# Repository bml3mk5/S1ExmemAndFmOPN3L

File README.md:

# Extended RAM & FM Synthesis Card for HITACHI MB-S1 (OPN3-L (YMF288) Version)

This is the extension card for HITACHI MB-S1 and Limelight. This is assembled two circuits
which are extended RAMs and FM Synthesis (YAMAHA YMF288(OPN3-L)). You can use two circuits, or just one of them.

## Used Tools

* KiCAD Version 5

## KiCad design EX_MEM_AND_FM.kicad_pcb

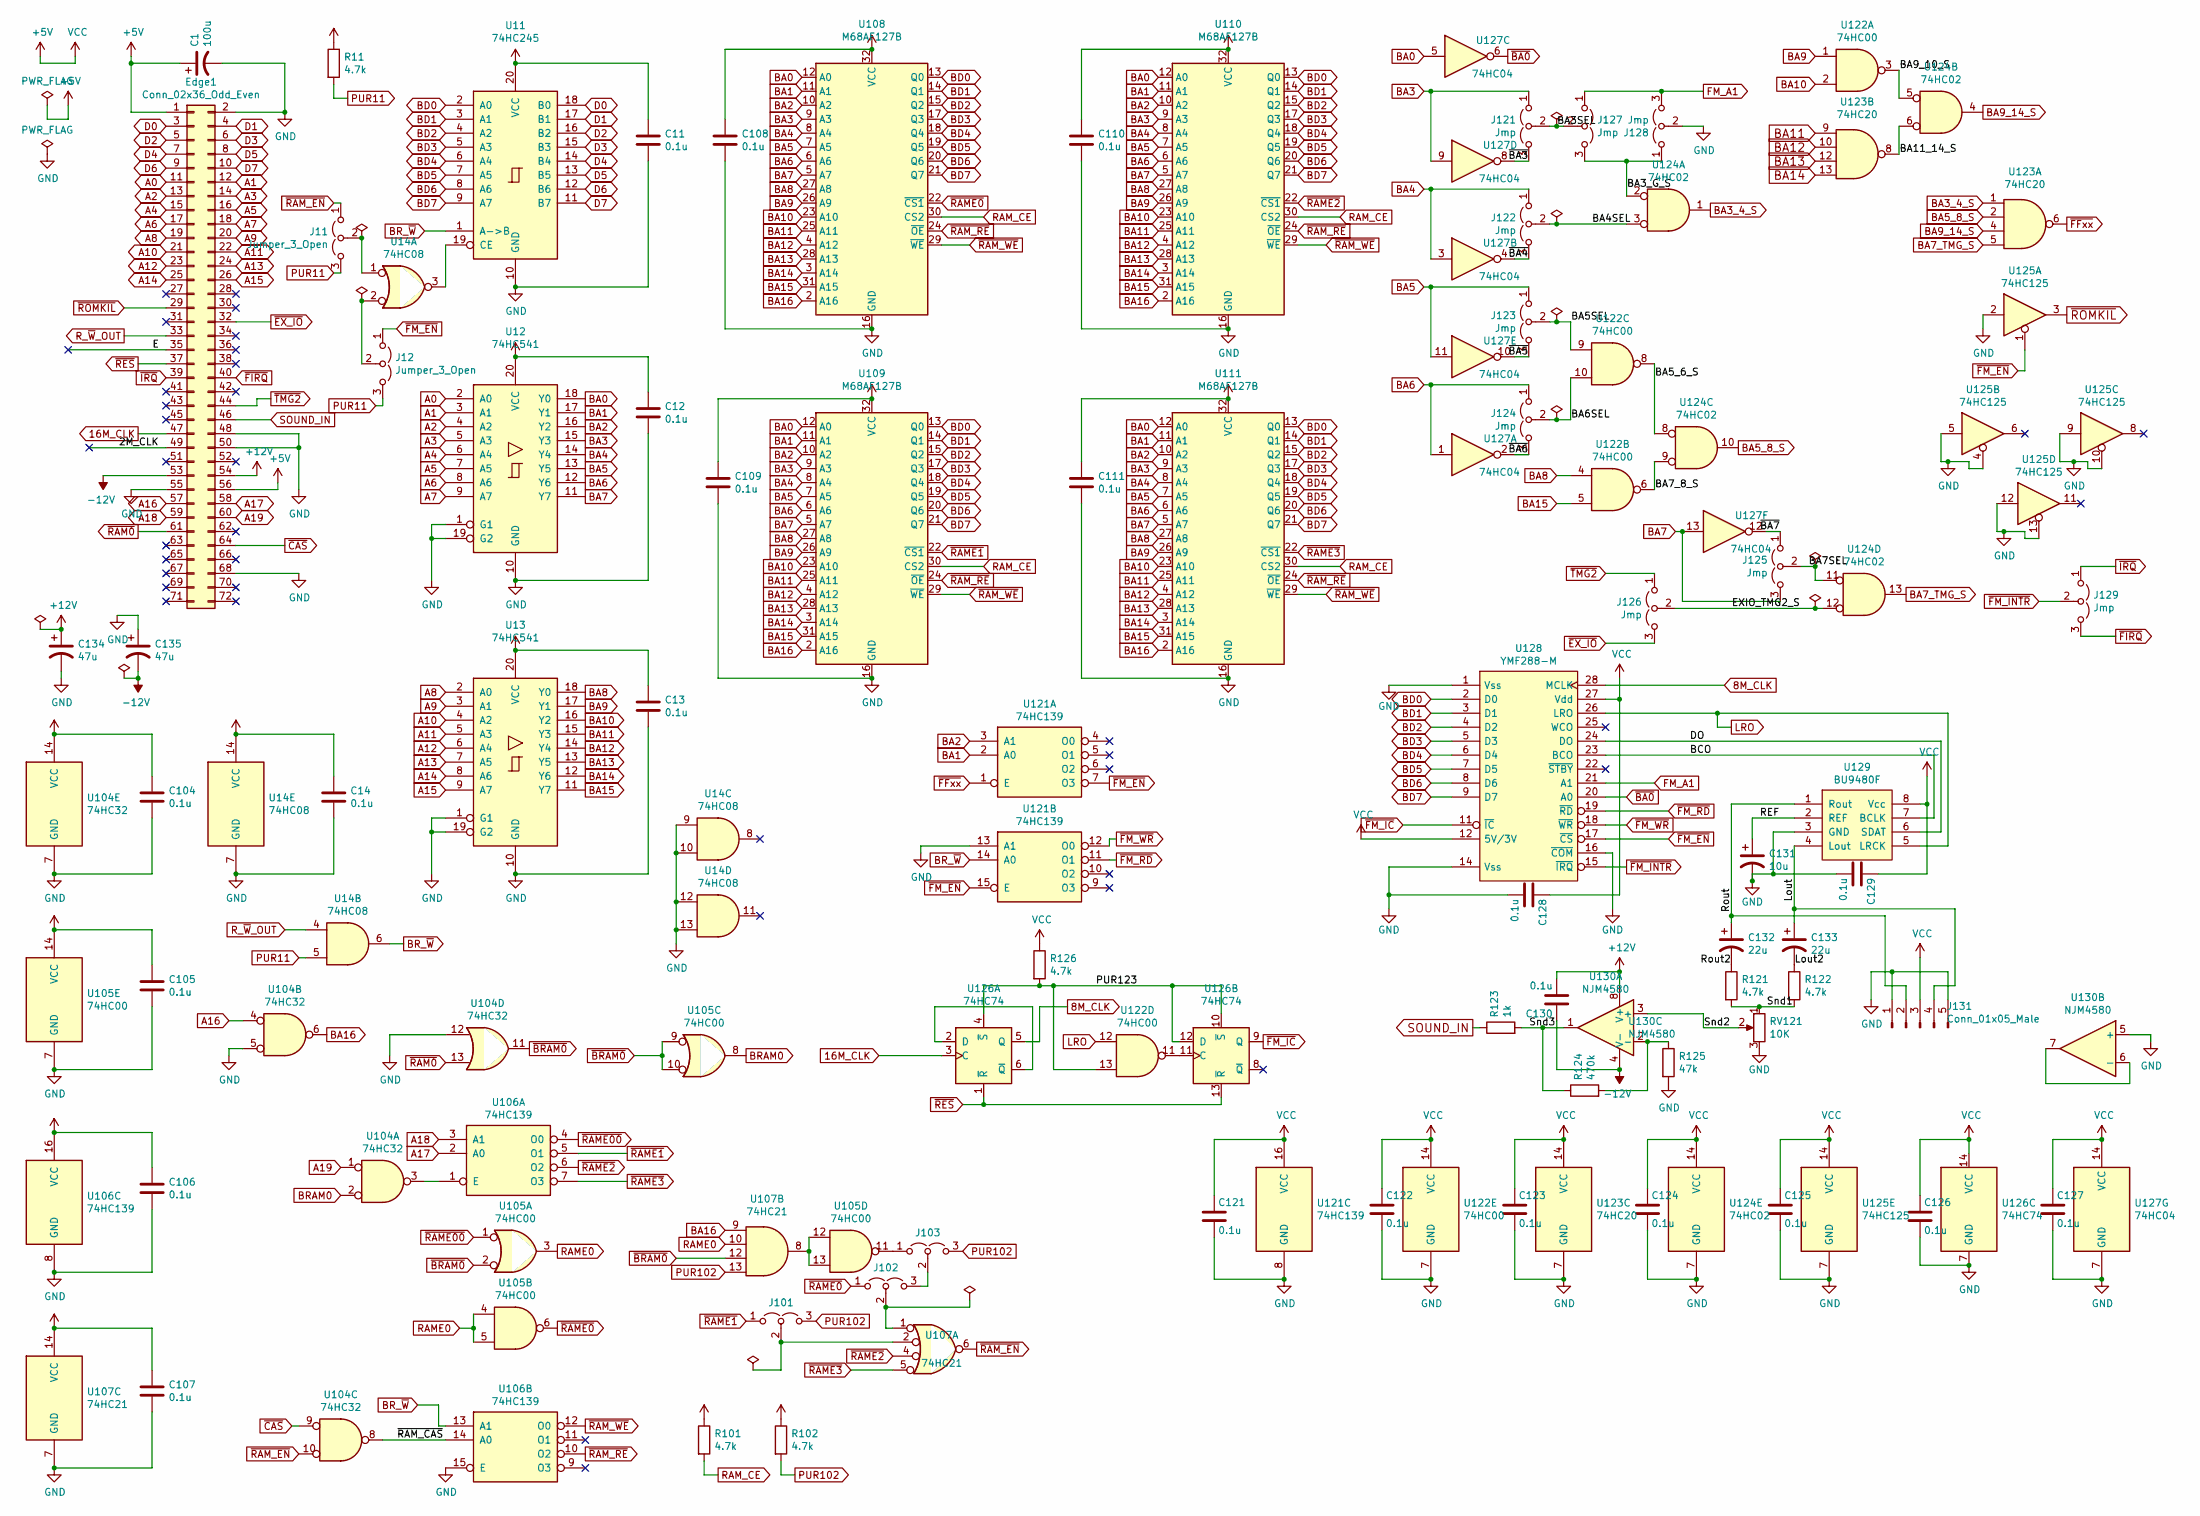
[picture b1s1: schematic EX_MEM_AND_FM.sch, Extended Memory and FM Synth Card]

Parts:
C1: 100u; CP_Radial_D6.3mm_P2.50mm
C11, C12, C13, C14, C104, C105, C106, C107, C108, C109, C110, C111, C121, C122, C123, C124, C125, C126, C127, C128, C129, C130: 0.1u; C_Disc_D3.0mm_W2.0mm_P2.50mm
C131: 10u; CP_Radial_D5.0mm_P2.50mm
C132, C133: 22u; CP_Radial_D5.0mm_P2.50mm
C134, C135: 47u; CP_Radial_D6.3mm_P2.50mm
Edge1: Conn_02x36_Odd_Even; CardEdge72
J11, J12, J101, J102, J103: Jumper_3_Open; Pin_Header_Straight_1x03_Pitch2.54mm
J121, J122, J123, J124, J125, J126, J127, J128, J129: Jmp; Pin_Header_Straight_1x03_Pitch2.54mm
J131: Conn_01x05_Male; Pin_Header_Angled_1x05_Pitch2.54mm
R11, R101, R102, R121, R122, R126: 4.7k; R_Axial_DIN0204_L3.6mm_D1.6mm_P2.54mm_Vertical
R123: 1k; R_Axial_DIN0204_L3.6mm_D1.6mm_P2.54mm_Vertical
R124: 470k; R_Axial_DIN0204_L3.6mm_D1.6mm_P2.54mm_Vertical
R125: 47k; R_Axial_DIN0204_L3.6mm_D1.6mm_P2.54mm_Vertical
RV121: 10K; Potentiometer_Trimmer_Bourns_3339P_Horizontal
U11: 74HC245; DIP-20_W7.62mm
U12, U13: 74HC541; DIP-20_W7.62mm
U14: 74HC08; DIP-14_W7.62mm
U104: 74HC32; DIP-14_W7.62mm
U105: 74HC00; DIP-14_W7.62mm
U106: 74HC139; DIP-16_W7.62mm
U107: 74HC21; DIP-14_W7.62mm
U108, U109, U110, U111: M68AF127B; SOIC-32
U121: 74HC139; DIP-16_W7.62mm_Socket
U122: 74HC00; DIP-14_W7.62mm_Socket
U123: 74HC20; DIP-14_W7.62mm_Socket
U124: 74HC02; DIP-14_W7.62mm_Socket
U125: 74HC125; DIP-14_W7.62mm_Socket
U126: 74HC74; DIP-14_W7.62mm_Socket
U127: 74HC04; DIP-14_W7.62mm
U128: YMF288-M; SOIC-28
U129: BU9480F; SOIC-8_3.9x4.9mm_Pitch1.27mm
U130: NJM4580; DIP-8_W7.62mm_Socket

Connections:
8M_CLK: U126.5 (Q), U128.28 (MCLK)
16M_CLK: Edge1.47, U126.3 (C)
+5V: C1.1, C11.1, C12.1, C13.1, C14.1, C104.1, C105.1, C106.1, C107.1, C108.1, C109.1, C110.1, C111.1, C121.1, C122.1, C123.1, C124.1, C125.1, C126.1, C127.1, C128.1, C129.1, Edge1.1, Edge1.56, J131.3, R11.1, R101.1, R102.1, R126.1, U11.20 (VCC), U12.20 (VCC), U13.20 (VCC), U14.14 (VCC), U104.14 (VCC), U105.14 (VCC), U106.16 (VCC), U107.14 (VCC), U108.32 (VCC), U109.32 (VCC), U110.32 (VCC), U111.32 (VCC), U121.16 (VCC), U122.14 (VCC), U123.14 (VCC), U124.14 (VCC), U125.14 (VCC), U126.14 (VCC), U127.14 (VCC), U128.12 (5V/3V), U128.27 (Vdd), U129.8 (Vcc)
+12V: C130.2, C134.1, Edge1.54, U130.8 (V+)
-12V: C130.1, C135.2, Edge1.53, U130.4 (V-)
/BA3SEL: J121.2 (C), J127.2 (C)
/BA3_G_S: J127.3 (B), J128.1 (A), U124.2
/BA4SEL: J122.2 (C), U124.3
/BA5SEL: J123.2 (C), U122.9
/BA5_6_S: U122.8, U124.8
/BA6SEL: J124.2 (C), U122.10
/BA7SEL: J125.2 (C), U124.11
/BA7_8_S: U122.6, U124.9
/BA9_10_S: U122.3, U124.5
/BA11_14_S: U123.8, U124.6
/BCO: U128.23 (BCO), U129.7 (BCLK)
/DO: U128.24 (DO), U129.6 (SDAT)
/EXIO_TMG2_S: J126.2 (C), U124.12
/Lout: C133.1, J131.4, U129.4 (Lout)
/Lout2: C133.2, R122.1
/PUR123: R126.2, U122.13, U126.4 (~S), U126.10 (~S), U126.12 (D)
/REF: C131.1, U129.2 (REF)
/Rout: C132.1, J131.2, U129.1 (Rout)
/Rout2: C132.2, R121.1
/Snd1: R121.2, R122.2, RV121.1
/Snd2: RV121.2, U130.3 (+)
/Snd3: R123.2, R124.1, U130.1
/~BA3: J121.3 (B), U127.8
/~BA4: J122.3 (B), U127.4
/~BA5: J123.3 (B), U127.10
/~BA6: J124.3 (B), U127.2
/~BA7: J125.1 (A), U127.12
/~RAM_CAS: U104.8, U106.14 (A0)
A0: Edge1.11, U12.2 (A0)
A1: Edge1.12, U12.3 (A1)
A2: Edge1.13, U12.4 (A2)
A3: Edge1.14, U12.5 (A3)
A4: Edge1.15, U12.6 (A4)
A5: Edge1.16, U12.7 (A5)
A6: Edge1.17, U12.8 (A6)
A7: Edge1.18, U12.9 (A7)
A8: Edge1.19, U13.2 (A0)
A9: Edge1.20, U13.3 (A1)
A10: Edge1.21, U13.4 (A2)
A11: Edge1.22, U13.5 (A3)
A12: Edge1.23, U13.6 (A4)
A13: Edge1.24, U13.7 (A5)
A14: Edge1.25, U13.8 (A6)
A15: Edge1.26, U13.9 (A7)
A16: Edge1.57, U104.4
A17: Edge1.58, U106.2 (A0)
A18: Edge1.59, U106.3 (A1)
A19: Edge1.60, U104.1
BA0: U12.18 (Y0), U108.12 (A0), U109.12 (A0), U110.12 (A0), U111.12 (A0), U127.5
BA1: U12.17 (Y1), U108.11 (A1), U109.11 (A1), U110.11 (A1), U111.11 (A1), U121.2 (A0)
BA2: U12.16 (Y2), U108.10 (A2), U109.10 (A2), U110.10 (A2), U111.10 (A2), U121.3 (A1)
BA3: J121.1 (A), U12.15 (Y3), U108.9 (A3), U109.9 (A3), U110.9 (A3), U111.9 (A3), U127.9
BA3_4_S: U123.1, U124.1
BA4: J122.1 (A), U12.14 (Y4), U108.8 (A4), U109.8 (A4), U110.8 (A4), U111.8 (A4), U127.3
BA5: J123.1 (A), U12.13 (Y5), U108.7 (A5), U109.7 (A5), U110.7 (A5), U111.7 (A5), U127.11
BA5_8_S: U123.2, U124.10
BA6: J124.1 (A), U12.12 (Y6), U108.6 (A6), U109.6 (A6), U110.6 (A6), U111.6 (A6), U127.1
BA7: J125.3 (B), U12.11 (Y7), U108.5 (A7), U109.5 (A7), U110.5 (A7), U111.5 (A7), U127.13
BA7_TMG_S: U123.5, U124.13
BA8: U13.18 (Y0), U108.27 (A8), U109.27 (A8), U110.27 (A8), U111.27 (A8), U122.4
BA9: U13.17 (Y1), U108.26 (A9), U109.26 (A9), U110.26 (A9), U111.26 (A9), U122.1
BA9_14_S: U123.4, U124.4
BA10: U13.16 (Y2), U108.23 (A10), U109.23 (A10), U110.23 (A10), U111.23 (A10), U122.2
BA11: U13.15 (Y3), U108.25 (A11), U109.25 (A11), U110.25 (A11), U111.25 (A11), U123.9
BA12: U13.14 (Y4), U108.4 (A12), U109.4 (A12), U110.4 (A12), U111.4 (A12), U123.10
BA13: U13.13 (Y5), U108.28 (A13), U109.28 (A13), U110.28 (A13), U111.28 (A13), U123.12
BA14: U13.12 (Y6), U108.3 (A14), U109.3 (A14), U110.3 (A14), U111.3 (A14), U123.13
BA15: U13.11 (Y7), U108.31 (A15), U109.31 (A15), U110.31 (A15), U111.31 (A15), U122.5
BA16: U104.6, U107.9, U108.2 (A16), U109.2 (A16), U110.2 (A16), U111.2 (A16)
BD0: U11.2 (A0), U108.13 (Q0), U109.13 (Q0), U110.13 (Q0), U111.13 (Q0), U128.2 (D0)
BD1: U11.3 (A1), U108.14 (Q1), U109.14 (Q1), U110.14 (Q1), U111.14 (Q1), U128.3 (D1)
BD2: U11.4 (A2), U108.15 (Q2), U109.15 (Q2), U110.15 (Q2), U111.15 (Q2), U128.4 (D2)
BD3: U11.5 (A3), U108.17 (Q3), U109.17 (Q3), U110.17 (Q3), U111.17 (Q3), U128.5 (D3)
BD4: U11.6 (A4), U108.18 (Q4), U109.18 (Q4), U110.18 (Q4), U111.18 (Q4), U128.6 (D4)
BD5: U11.7 (A5), U108.19 (Q5), U109.19 (Q5), U110.19 (Q5), U111.19 (Q5), U128.7 (D5)
BD6: U11.8 (A6), U108.20 (Q6), U109.20 (Q6), U110.20 (Q6), U111.20 (Q6), U128.8 (D6)
BD7: U11.9 (A7), U108.21 (Q7), U109.21 (Q7), U110.21 (Q7), U111.21 (Q7), U128.9 (D7)
BRAM0: U104.2, U105.8
BR_~W: U11.1 (A->B), U14.6, U106.13 (A1), U121.14 (A0)
D0: Edge1.3, U11.18 (B0)
D1: Edge1.4, U11.17 (B1)
D2: Edge1.5, U11.16 (B2)
D3: Edge1.6, U11.15 (B3)
D4: Edge1.7, U11.14 (B4)
D5: Edge1.8, U11.13 (B5)
D6: Edge1.9, U11.12 (B6)
D7: Edge1.10, U11.11 (B7)
FM_A1: J127.1 (A), J128.3 (B), U128.21 (A1)
GND: C1.2, C11.2, C12.2, C13.2, C14.2, C104.2, C105.2, C106.2, C107.2, C108.2, C109.2, C110.2, C111.2, C121.2, C122.2, C123.2, C124.2, C125.2, C126.2, C127.2, C128.2, C129.2, C131.2, C134.2, C135.1, Edge1.2, Edge1.48, Edge1.50, Edge1.55, Edge1.68, J128.2 (C), J131.1, J131.5, R125.2, RV121.3, U11.10 (GND), U12.1 (G1), U12.10 (GND), U12.19 (G2), U13.1 (G1), U13.10 (GND), U13.19 (G2), U14.7 (GND), U14.9, U14.10, U14.12, U14.13, U104.5, U104.7 (GND), U104.12, U105.7 (GND), U106.8 (GND), U106.15 (E), U107.7 (GND), U108.16 (GND), U109.16 (GND), U110.16 (GND), U111.16 (GND), U121.8 (GND), U121.13 (A1), U122.7 (GND), U123.7 (GND), U124.7 (GND), U125.2, U125.4, U125.5, U125.7 (GND), U125.9, U125.10, U125.12, U125.13, U126.7 (GND), U127.7 (GND), U128.1 (Vss), U128.14 (Vss), U128.16 (~COM), U129.3 (GND), U130.5 (+)
LRO: U122.12, U128.26 (LRO), U129.5 (LRCK)
unnamed: J11.2 (C), U14.1
unnamed: J12.2 (C), U14.2
unnamed: J101.2 (C), U107.2
unnamed: J102.2 (C), U107.1
unnamed: J102.3 (B), J103.2 (C)
unnamed: J103.1 (A), U105.11
unnamed: R124.2, R125.1, U130.2 (-)
unnamed: U11.19 (CE), U14.3
unnamed: U104.3, U106.1 (E)
unnamed: U105.12, U105.13, U107.8
unnamed: U122.11, U126.11 (C)
unnamed: U126.2 (D), U126.6 (~Q)
unnamed: U130.6 (-), U130.7
PUR11: J11.3 (B), J12.3 (B), R11.2, U14.5
PUR102: J101.3 (B), J103.3 (B), R102.2, U107.13
RAME0: U105.3, U105.4, U105.5, U107.10
RAM_CE: R101.2, U108.30 (CS2), U109.30 (CS2), U110.30 (CS2), U111.30 (CS2)
R_~W~_OUT: Edge1.33, U14.4
SOUND_IN: Edge1.46, R123.1
~BA0: U127.6, U128.20 (A0)
~BRAM0: U104.11, U105.2, U105.9, U105.10, U107.12
~CAS: Edge1.64, U104.9
~EX_IO: Edge1.32, J126.3 (B)
~FFxx: U121.1 (E), U123.6
~FIRQ: Edge1.40, J129.3 (B)
~FM_EN: J12.1 (A), U121.7 (O3), U121.15 (E), U125.1, U128.17 (~CS)
~FM_IC: U126.9 (Q), U128.11 (~IC)
~FM_INTR: J129.2 (C), U128.15 (~IRQ)
~FM_RD: U121.11 (O1), U128.19 (~RD)
~FM_WR: U121.12 (O0), U128.18 (~WR)
~IRQ: Edge1.39, J129.1 (A)
~RAM0: Edge1.61, U104.13
~RAME00: U105.1, U106.4 (O0)
~RAME0: J102.1 (A), U105.6, U108.22 (~CS1)
~RAME1: J101.1 (A), U106.5 (O1), U109.22 (~CS1)
~RAME2: U106.6 (O2), U107.4, U110.22 (~CS1)
~RAME3: U106.7 (O3), U107.5, U111.22 (~CS1)
~RAM_EN: J11.1 (A), U104.10, U107.6
~RAM_RE: U106.10 (O2), U108.24 (~OE), U109.24 (~OE), U110.24 (~OE), U111.24 (~OE)
~RAM_WE: U106.12 (O0), U108.29 (~WE), U109.29 (~WE), U110.29 (~WE), U111.29 (~WE)
~RES: Edge1.37, U126.1 (~R), U126.13 (~R)
~ROMKIL: Edge1.29, U125.3
~TMG2: Edge1.44, J126.1 (A)

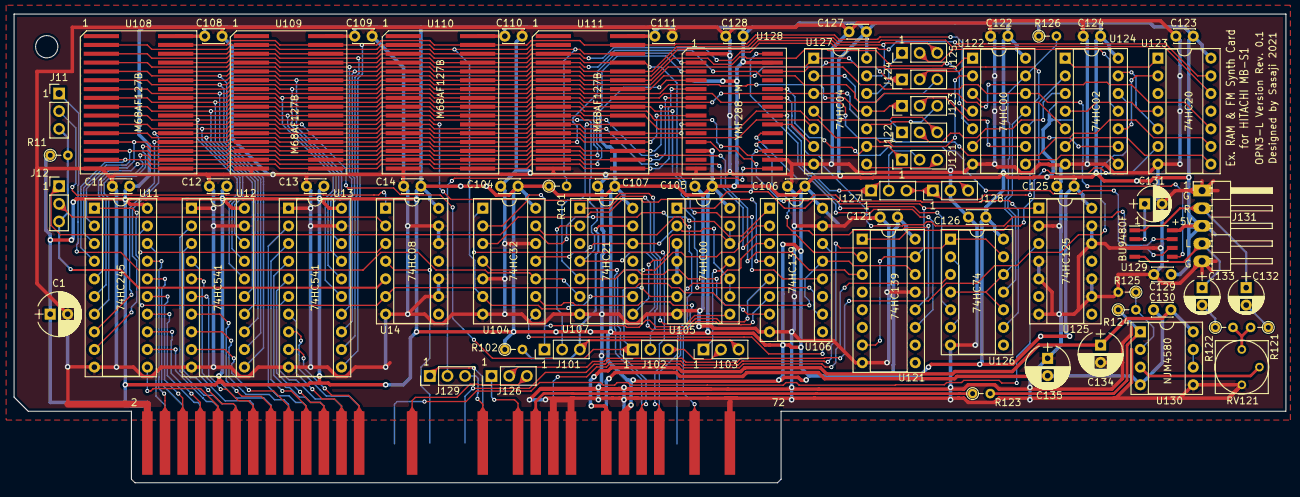
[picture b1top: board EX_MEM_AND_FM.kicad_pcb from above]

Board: 2 copper layers, 183.0 x 67.4 mm, 76 parts (0 on the bottom side), 138 nets.

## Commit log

2023-03-01 Revision 0.1
2023-07-09 Add an image
